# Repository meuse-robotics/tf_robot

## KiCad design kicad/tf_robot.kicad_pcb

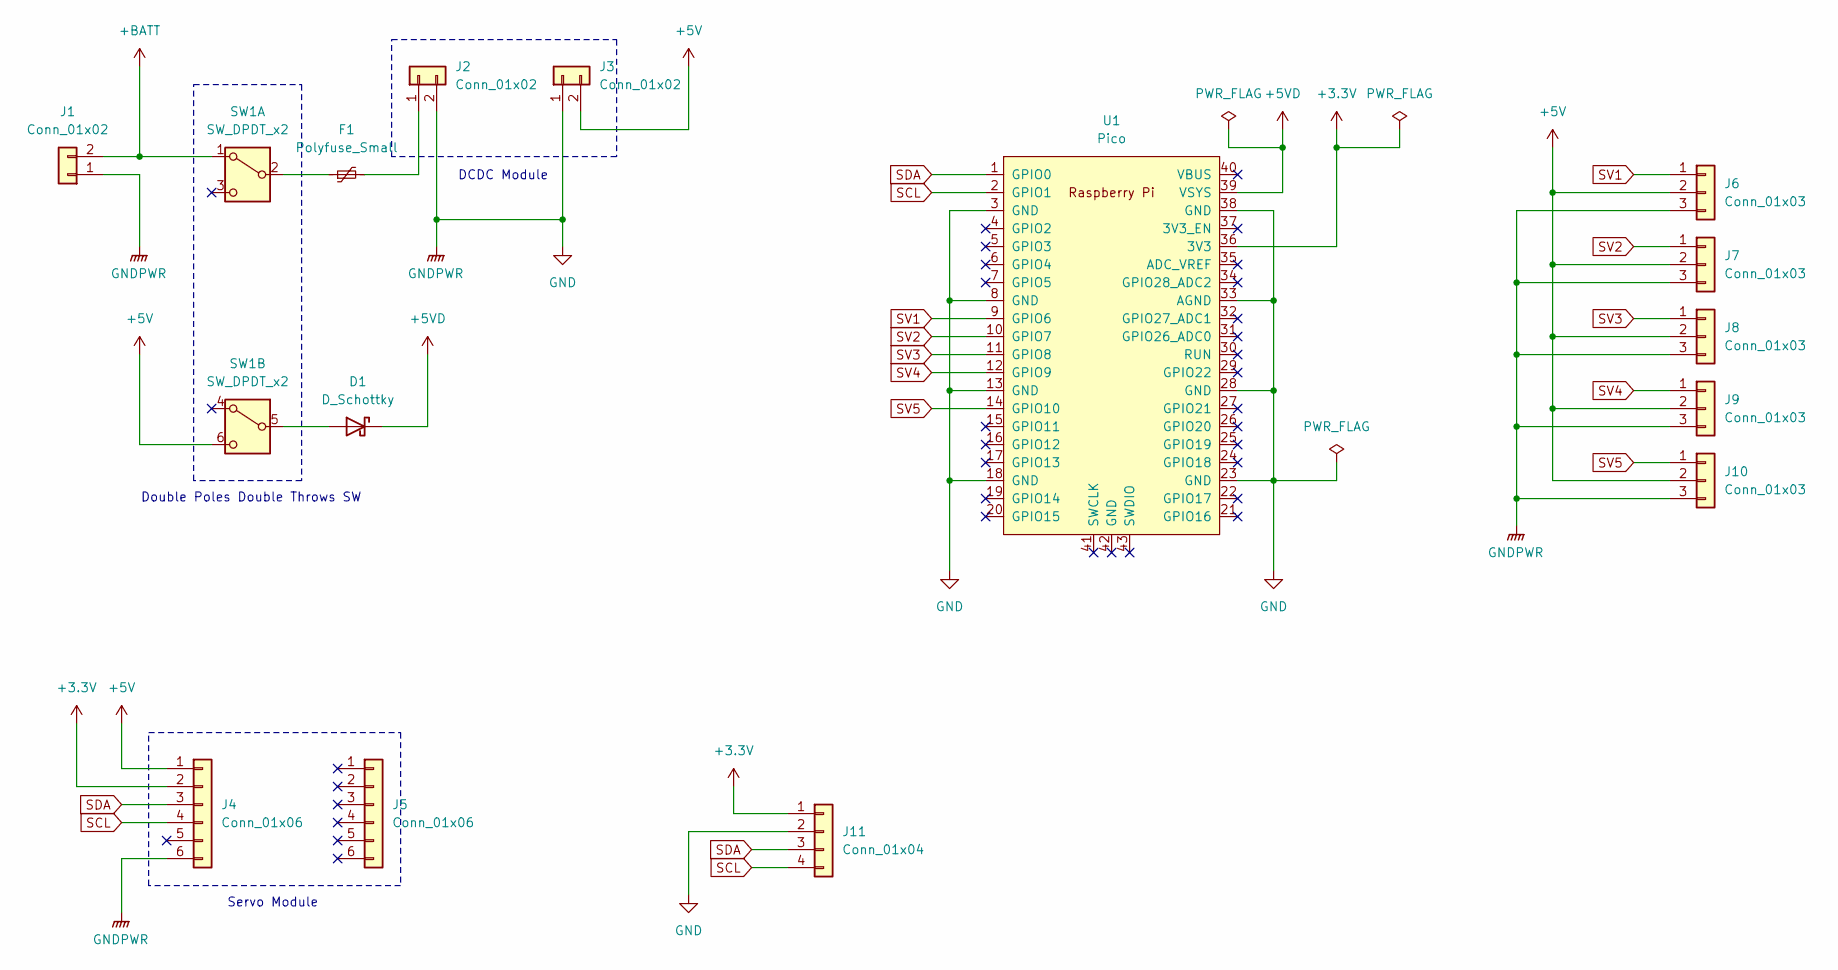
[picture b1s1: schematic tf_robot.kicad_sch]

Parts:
D1: D_Schottky; D_A-405_P10.16mm_Horizontal
F1: Polyfuse_Small; Fuse_BelFuse_0ZRE0055FF_L14.0mm_W4.1mm
J1: Conn_01x02; PinHeader_1x02_P2.54mm_Vertical
J2, J3: Conn_01x02; TerminalBlock_bornier-2_P5.08mm
J4, J5: Conn_01x06; PinHeader_1x06_P2.54mm_Vertical
J6, J7, J8, J9, J10: Conn_01x03; PinHeader_1x03_P2.54mm_Vertical
J11: Conn_01x04; PinHeader_1x04_P2.54mm_Vertical
SW1: SW_DPDT_x2; SW_CK_JS202011CQN_DPDT_Straight
U1: Pico; RPi_Pico_SMD_TH

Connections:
+3.3V: J4.2, J11.1, U1.36 (3V3)
+5V: J3.2, J4.1, J6.2, J7.2, J8.2, J9.2, J10.2, SW1.6 (C)
+5VD: D1.1 (K), U1.39 (VSYS)
+BATT: J1.2, SW1.1 (A)
GND: J1.1, J2.2, J3.1, J4.6, J6.3, J7.3, J8.3, J9.3, J10.3, J11.2, U1.3 (GND), U1.8 (GND), U1.13 (GND), U1.18 (GND), U1.23 (GND), U1.28 (GND), U1.33 (AGND), U1.38 (GND)
unnamed: D1.2 (A), SW1.5 (B)
unnamed: F1.2, J2.1
unnamed: F1.1, SW1.2 (B)
SCL: J4.4, J11.4, U1.2 (GPIO1)
SDA: J4.3, J11.3, U1.1 (GPIO0)
SV1: J6.1, U1.9 (GPIO6)
SV2: J7.1, U1.10 (GPIO7)
SV3: J8.1, U1.11 (GPIO8)
SV4: J9.1, U1.12 (GPIO9)
SV5: J10.1, U1.14 (GPIO10)

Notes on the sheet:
DCDC Module
Servo Module
Double Poles Double Throws SW

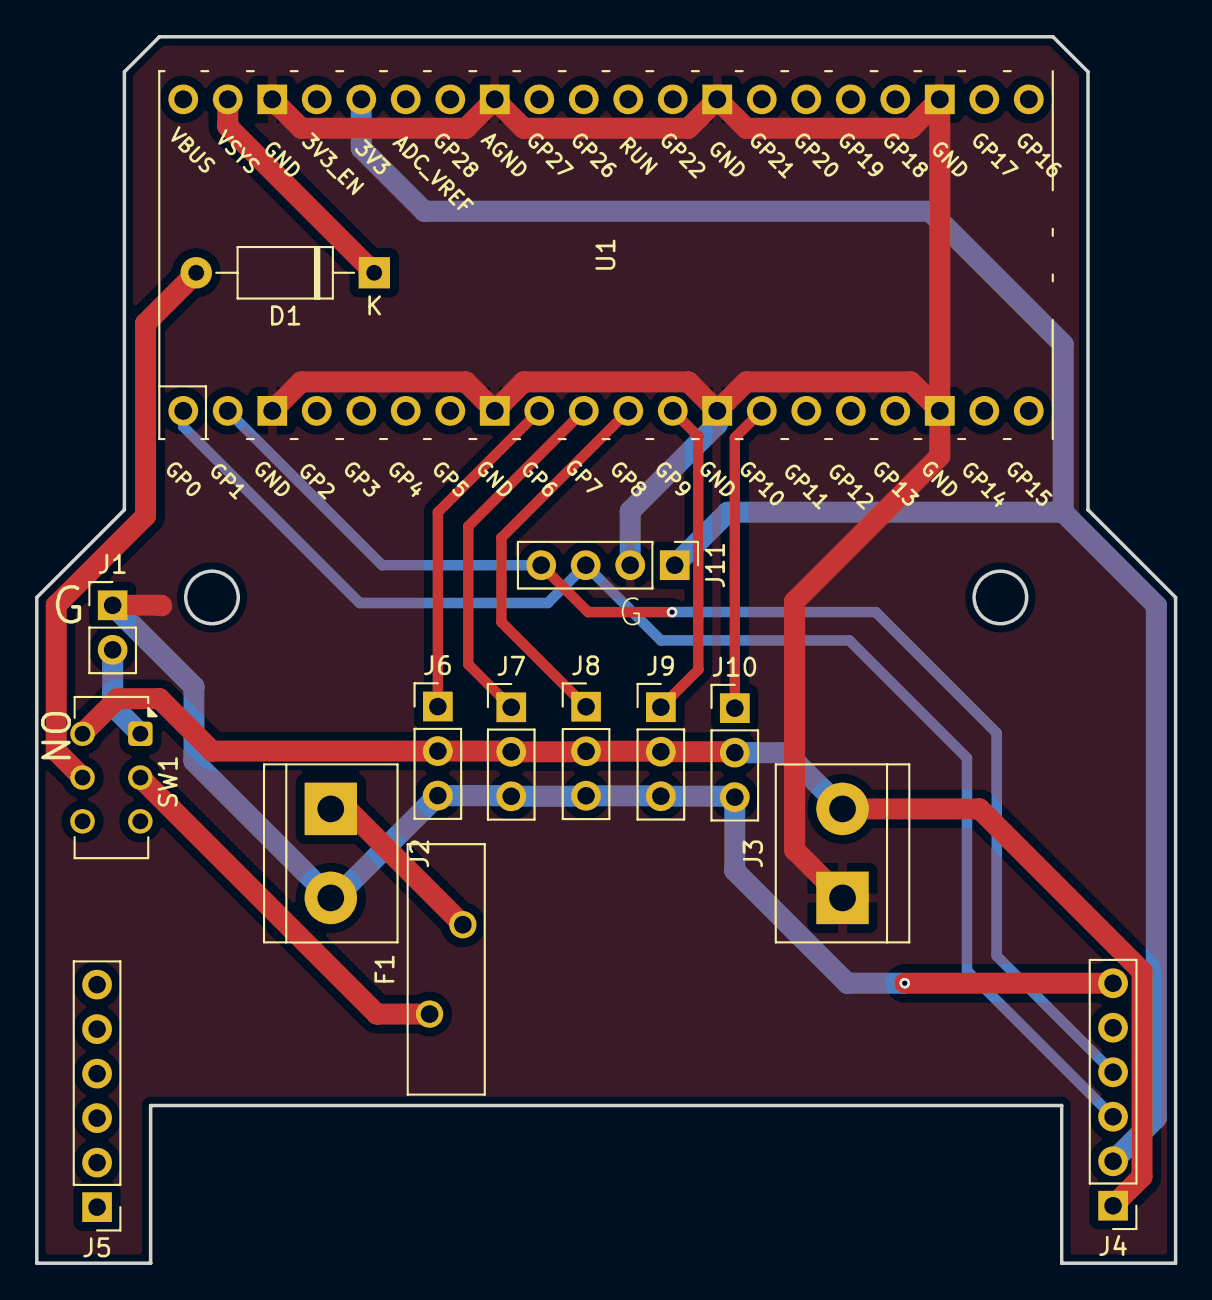
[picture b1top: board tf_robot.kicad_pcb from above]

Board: 2 copper layers, 65.0 x 70.0 mm, 15 parts (0 on the bottom side), 15 nets.

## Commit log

2024-12-05 Add files
2025-01-06 Update robot_webserver.py
    correct typo
